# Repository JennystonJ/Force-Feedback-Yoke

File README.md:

# Force Feedback Yoke
A DIY force feedback flight simulator yoke using brushless motors, load cells, and custom firmware to provide simulated control forces.

---

## Overview
- BLDC motors for pitch and roll using torque control.
- Support for load cells. Currently used for force feedback assist (reduces drag felt by user).
- STM32 microcontroller running custom firmware with FOC inspired by SimpleFOC.
- Desktop app for monitoring, setting parameters, handling communication between device and Microsoft Flight Simulator, and calculating forces.

## Features
- Support for 2 axis current/torque control.
- Force feedback assist using load cells to reduce drag.
- USB HID communication.
- Support for constant, spring, and damper effects on both axes.
- Axes travel is software adjustable using the motor as a virtual stopper.

## Technical Details
- Motors: 2 * 57BL95S06-210TF9
- Motor Drivers: 2 * DRV8301 boards
- Microcontroller: STM32H743VGT6
- Sensors:
	- 2 * three phase shunt-based in-line current sensors (INA241)
	- 2 * encoders using AB output (65536 CPR) for lower latency (MT6835)
	- 2 * load cells (20kg) (roll load cell support for mechanical is in progress)
- Software: C firmware, C# desktop app

## Mechanical
- Total pitch travel: ~177 mm, roll travel: ~270 deg
- 3D printed components, aluminum V-slot extrusion for frame. T-slot is also compatible.
- Bearings on all axes, two linear guide rails for linear motion on pitch axis.
- Two-stage belt drive for pitch axis, single belt for roll axis.
- Designed to be modular.

## Desktop App
- Displays live axes positions, and axes force/torque
- Implements custom USB HID communication with device and communication with Microsoft Flight Simulator through SimConnect API.
- Currently supports 2 different force feedback effects, with more being added and existing effects being refined:
	- Supported effects
		- Airspeed stiffness (increases centering force with airspeed)
		- Elevator weight (a constant elevator down force with engine RPM dependent self-centering force).
- Adjustable gains for all force feedback effects in GUI for both pitch and roll axes.
- Travel for both axes are adjustable in GUI.

## Acknowledgements
Algorithms (Clarke & Park transforms) from [SimpleFOC](https://github.com/simplefoc/Arduino-FOC) (MIT License). See LICENSES/LICENSE-SIMPLEFOC.txt for full license.

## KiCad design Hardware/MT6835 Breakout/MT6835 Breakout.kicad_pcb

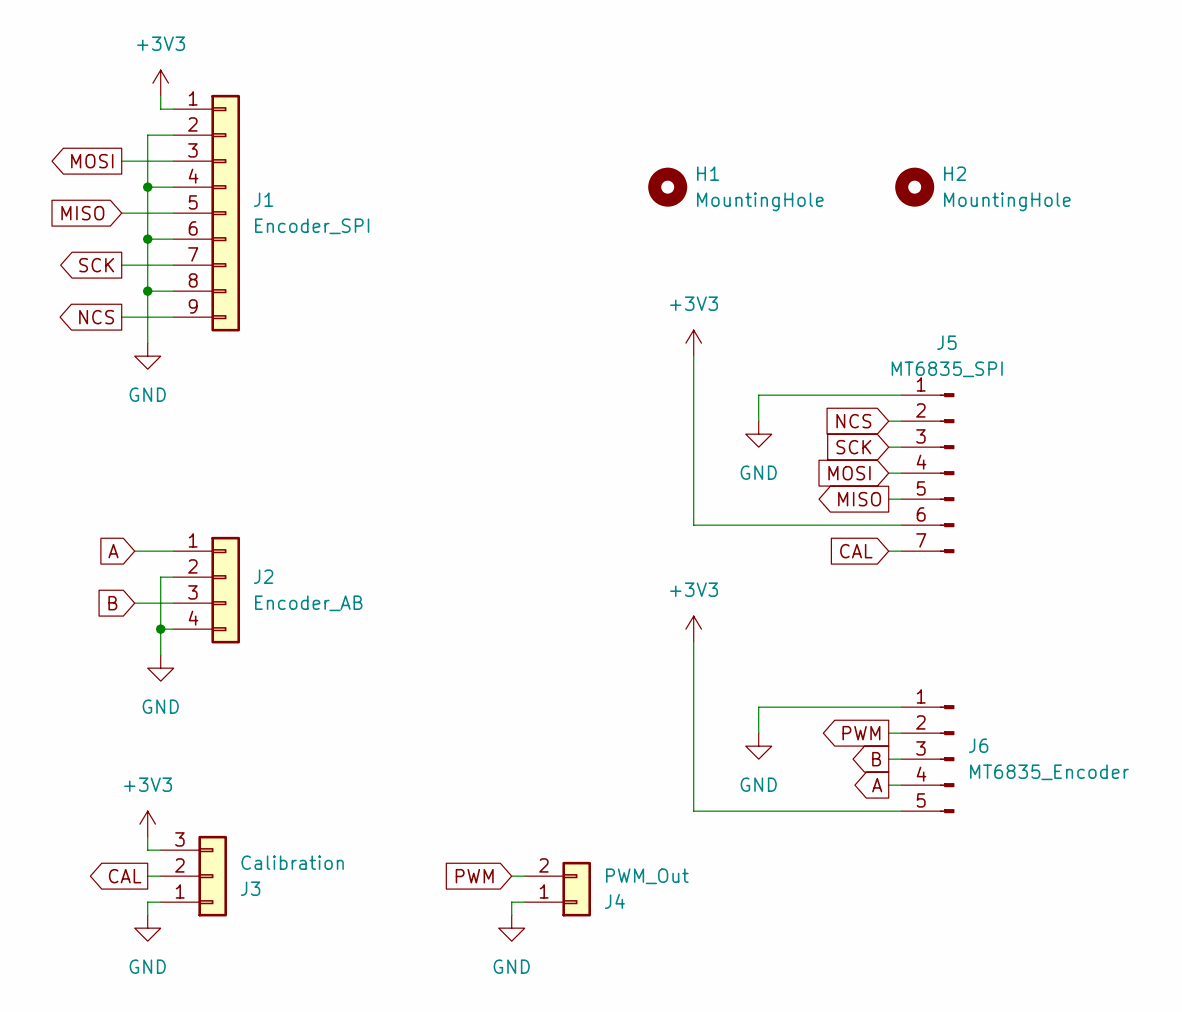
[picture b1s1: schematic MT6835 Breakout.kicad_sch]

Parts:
H1, H2: MountingHole; MountingHole_2.2mm_M2
J1: Encoder_SPI; JST_PH_B9B-PH-K_1x09_P2.00mm_Vertical
J2: Encoder_AB; JST_PH_B4B-PH-K_1x04_P2.00mm_Vertical
J3: Calibration; PinHeader_1x03_P2.54mm_Vertical
J4: PWM_Out; PinHeader_1x02_P2.54mm_Vertical
J5: MT6835_SPI; PinHeader_1x07_P2.54mm_Vertical
J6: MT6835_Encoder; PinHeader_1x05_P2.54mm_Vertical

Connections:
+3V3: J1.1, J3.3, J5.6, J6.5
A: J2.1, J6.4
B: J2.3, J6.3
CAL: J3.2, J5.7
GND: J1.2, J1.4, J1.6, J1.8, J2.2, J2.4, J3.1, J4.1, J5.1, J6.1
MISO: J1.5, J5.5
MOSI: J1.3, J5.4
NCS: J1.9, J5.2
PWM: J4.2, J6.2
SCK: J1.7, J5.3

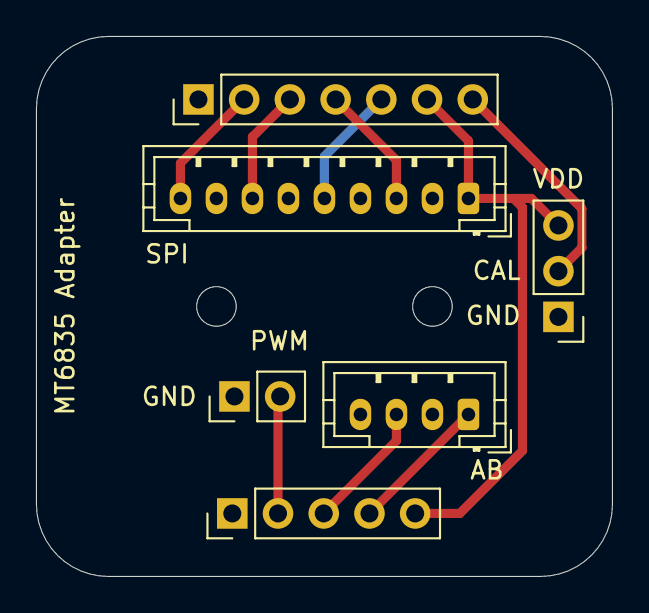
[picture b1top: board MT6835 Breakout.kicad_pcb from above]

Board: 2 copper layers, 32.0 x 30.0 mm, 8 parts (0 on the bottom side), 10 nets.

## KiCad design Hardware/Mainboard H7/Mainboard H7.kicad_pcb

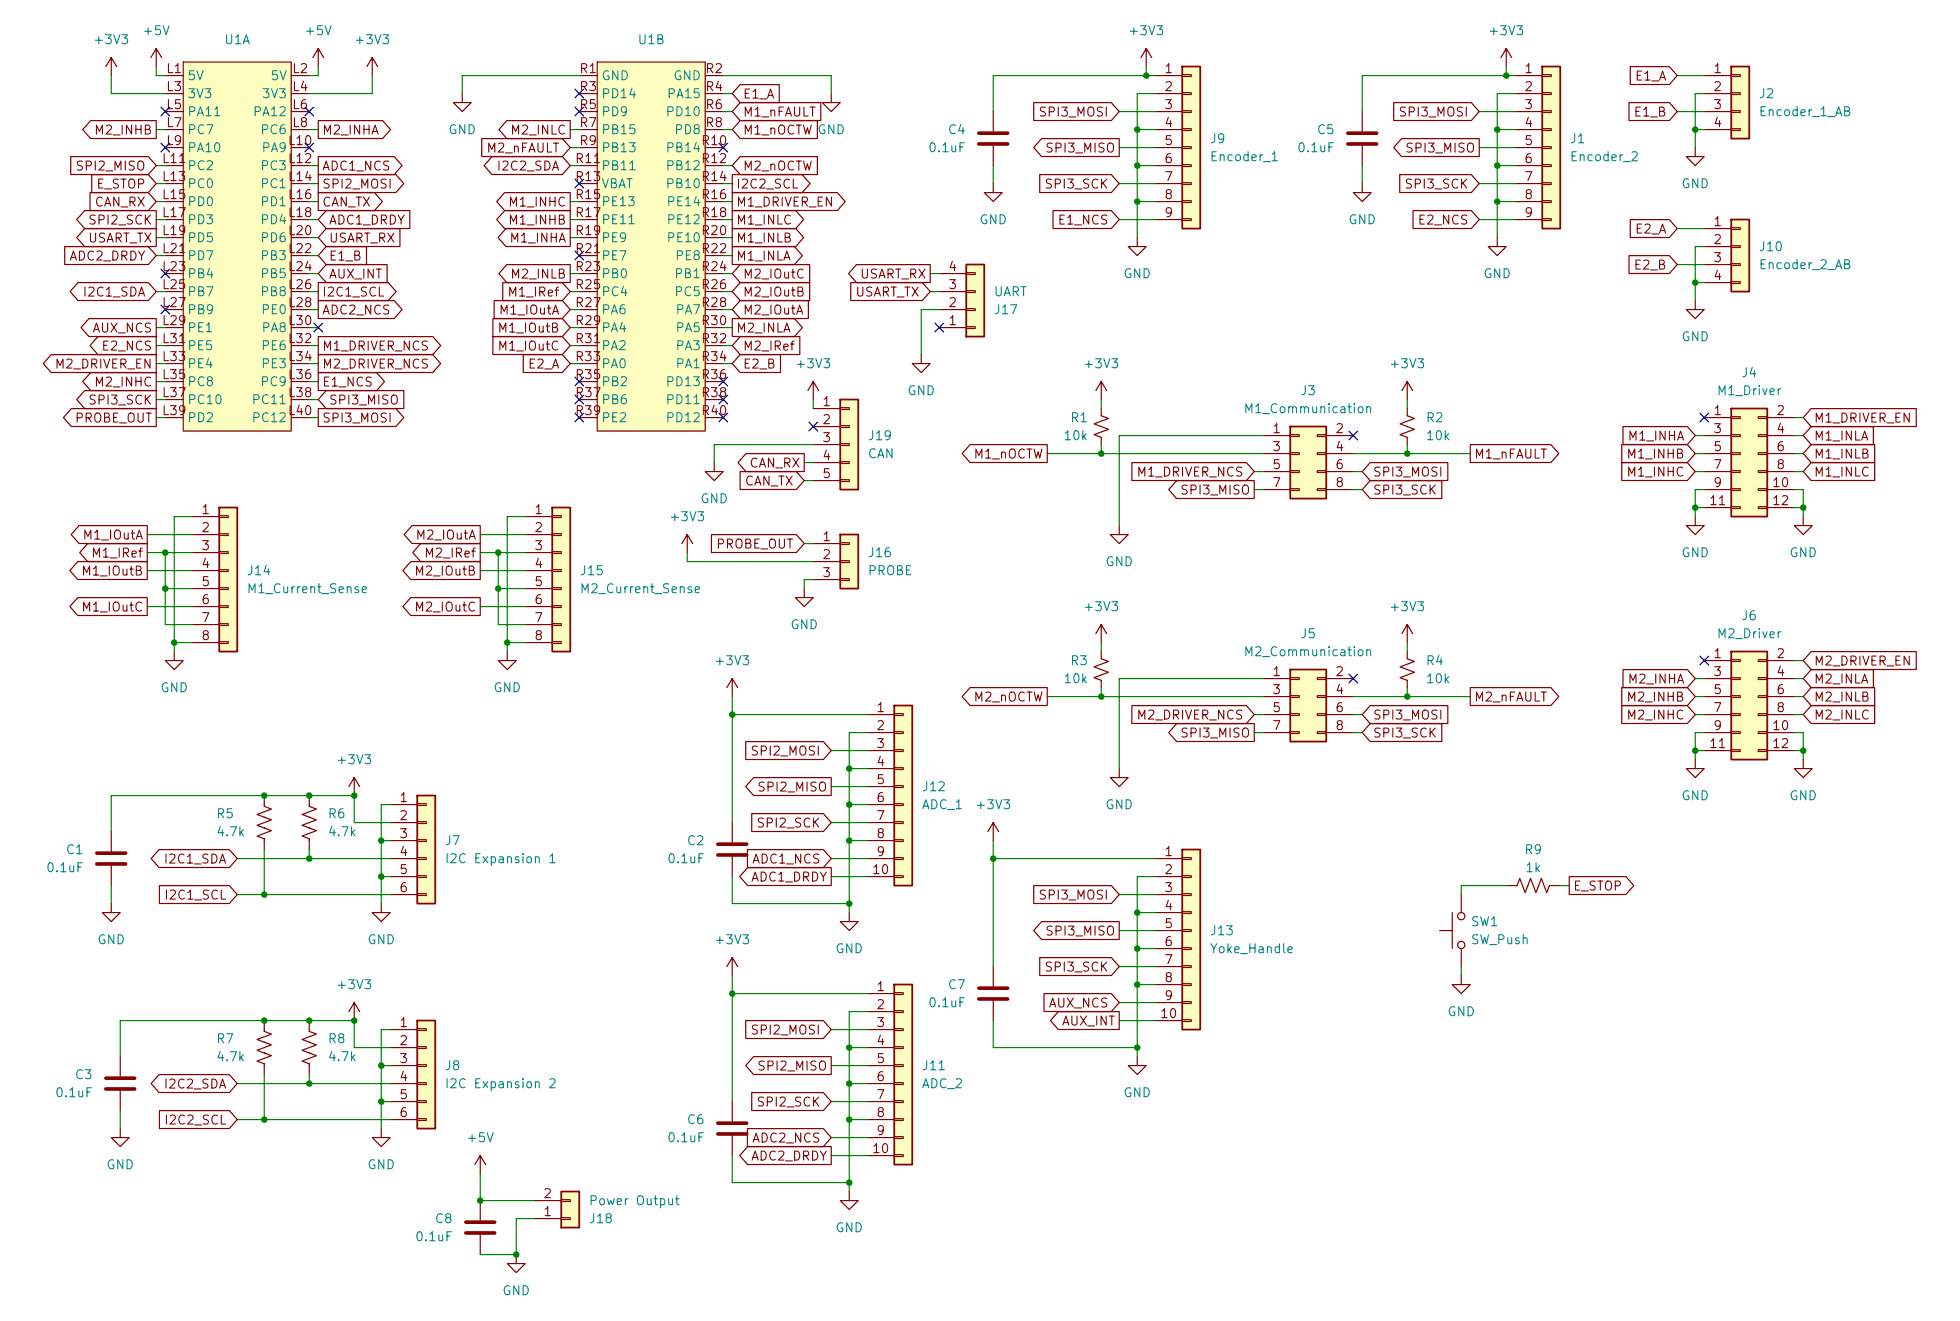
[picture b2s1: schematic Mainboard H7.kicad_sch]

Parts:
C1, C2, C3, C4, C5, C6, C7, C8: 0.1uF; C_0603_1608Metric_Pad1.08x0.95mm_HandSolder
J1: Encoder_2; JST_PH_B9B-PH-K_1x09_P2.00mm_Vertical
J2: Encoder_1_AB; JST_PH_B4B-PH-K_1x04_P2.00mm_Vertical
J3: M1_Communication; PinHeader_2x04_P2.54mm_Vertical
J4: M1_Driver; PinHeader_2x06_P2.54mm_Vertical
J5: M2_Communication; PinHeader_2x04_P2.54mm_Vertical
J6: M2_Driver; PinHeader_2x06_P2.54mm_Vertical
J7: I2C Expansion 1; JST_PH_B6B-PH-K_1x06_P2.00mm_Vertical
J8: I2C Expansion 2; JST_PH_B6B-PH-K_1x06_P2.00mm_Vertical
J9: Encoder_1; JST_PH_B9B-PH-K_1x09_P2.00mm_Vertical
J10: Encoder_2_AB; JST_PH_B4B-PH-K_1x04_P2.00mm_Vertical
J11: ADC_2; JST_PH_B10B-PH-K_1x10_P2.00mm_Vertical
J12: ADC_1; JST_PH_B10B-PH-K_1x10_P2.00mm_Vertical
J13: Yoke_Handle; JST_PH_B10B-PH-K_1x10_P2.00mm_Vertical
J14: M1_Current_Sense; JST_PH_B8B-PH-K_1x08_P2.00mm_Vertical
J15: M2_Current_Sense; JST_PH_B8B-PH-K_1x08_P2.00mm_Vertical
J16: PROBE; PinHeader_1x03_P2.54mm_Vertical
J17: UART; PinHeader_1x04_P2.54mm_Vertical
J18: Power Output; PinHeader_1x02_P2.54mm_Vertical
J19: CAN; PinHeader_1x05_P2.54mm_Vertical
R1, R2, R3, R4: 10k; R_0603_1608Metric_Pad0.98x0.95mm_HandSolder
R5, R6, R7, R8: 4.7k; R_0603_1608Metric_Pad0.98x0.95mm_HandSolder
R9: 1k; R_0603_1608Metric_Pad0.98x0.95mm_HandSolder
SW1: SW_Push; JST_PH_B2B-PH-K_1x02_P2.00mm_Vertical
U1: FK743M3-VGT6

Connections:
+3V3: C1.1, C2.1, C3.1, C4.1, C5.1, C6.1, C7.1, J1.1, J7.2, J8.2, J9.1, J11.1, J12.1, J13.1, J16.2, J19.1, R1.1, R2.1, R3.1, R4.1, R5.1, R6.1, R7.1, R8.1, U1.L3 (3V3), U1.L4 (3V3)
+5V: C8.1, J18.2, U1.L1 (5V), U1.L2 (5V)
ADC1_DRDY: J12.10, U1.L18 (PD4)
ADC1_NCS: J12.9, U1.L12 (PC3)
ADC2_DRDY: J11.10, U1.L21 (PD7)
ADC2_NCS: J11.9, U1.L28 (PE0)
AUX_INT: J13.10, U1.L24 (PB5)
AUX_NCS: J13.9, U1.L29 (PE1)
CAN_RX: J19.4, U1.L15 (PD0)
CAN_TX: J19.5, U1.L16 (PD1)
E1_A: J2.1, U1.R4 (PA15)
E1_B: J2.3, U1.L22 (PB3)
E1_NCS: J9.9, U1.L36 (PC9)
E2_A: J10.1, U1.R33 (PA0)
E2_B: J10.3, U1.R34 (PA1)
E2_NCS: J1.9, U1.L31 (PE5)
E_STOP: R9.1, U1.L13 (PC0)
GND: C1.2, C2.2, C3.2, C4.2, C5.2, C6.2, C7.2, C8.2, J1.2, J1.4, J1.6, J1.8, J2.2, J2.4, J3.1, J4.9, J4.10, J4.11, J4.12, J5.1, J6.9, J6.10, J6.11, J6.12, J7.1, J7.3, J7.5, J8.1, J8.3, J8.5, J9.2, J9.4, J9.6, J9.8, J10.2, J10.4, J11.2, J11.4, J11.6, J11.8, J12.2, J12.4, J12.6, J12.8, J13.2, J13.4, J13.6, J13.8, J14.1, J14.8, J15.1, J15.8, J16.3, J17.2, J18.1, J19.3, SW1.1, U1.R1 (GND), U1.R2 (GND)
I2C1_SCL: J7.6, R5.2, U1.L26 (PB8)
I2C1_SDA: J7.4, R6.2, U1.L25 (PB7)
I2C2_SCL: J8.6, R7.2, U1.R14 (PB10)
I2C2_SDA: J8.4, R8.2, U1.R11 (PB11)
M1_DRIVER_EN: J4.2, U1.R16 (PE14)
M1_DRIVER_NCS: J3.5, U1.L32 (PE6)
M1_INHA: J4.3, U1.R19 (PE9)
M1_INHB: J4.5, U1.R17 (PE11)
M1_INHC: J4.7, U1.R15 (PE13)
M1_INLA: J4.4, U1.R22 (PE8)
M1_INLB: J4.6, U1.R20 (PE10)
M1_INLC: J4.8, U1.R18 (PE12)
M1_IOutA: J14.2, U1.R27 (PA6)
M1_IOutB: J14.4, U1.R29 (PA4)
M1_IOutC: J14.6, U1.R31 (PA2)
M1_IRef: J14.3, J14.5, J14.7, U1.R25 (PC4)
M1_nFAULT: J3.4, R2.2, U1.R6 (PD10)
M1_nOCTW: J3.3, R1.2, U1.R8 (PD8)
M2_DRIVER_EN: J6.2, U1.L33 (PE4)
M2_DRIVER_NCS: J5.5, U1.L34 (PE3)
M2_INHA: J6.3, U1.L8 (PC6)
M2_INHB: J6.5, U1.L7 (PC7)
M2_INHC: J6.7, U1.L35 (PC8)
M2_INLA: J6.4, U1.R30 (PA5)
M2_INLB: J6.6, U1.R23 (PB0)
M2_INLC: J6.8, U1.R7 (PB15)
M2_IOutA: J15.2, U1.R28 (PA7)
M2_IOutB: J15.4, U1.R26 (PC5)
M2_IOutC: J15.6, U1.R24 (PB1)
M2_IRef: J15.3, J15.5, J15.7, U1.R32 (PA3)
M2_nFAULT: J5.4, R4.2, U1.R9 (PB13)
M2_nOCTW: J5.3, R3.2, U1.R12 (PB12)
unnamed: R9.2, SW1.2
PROBE_OUT: J16.1, U1.L39 (PD2)
SPI2_MISO: J11.5, J12.5, U1.L11 (PC2)
SPI2_MOSI: J11.3, J12.3, U1.L14 (PC1)
SPI2_SCK: J11.7, J12.7, U1.L17 (PD3)
SPI3_MISO: J1.5, J3.7, J5.7, J9.5, J13.5, U1.L38 (PC11)
SPI3_MOSI: J1.3, J3.6, J5.6, J9.3, J13.3, U1.L40 (PC12)
SPI3_SCK: J1.7, J3.8, J5.8, J9.7, J13.7, U1.L37 (PC10)
USART_RX: J17.4, U1.L20 (PD6)
USART_TX: J17.3, U1.L19 (PD5)

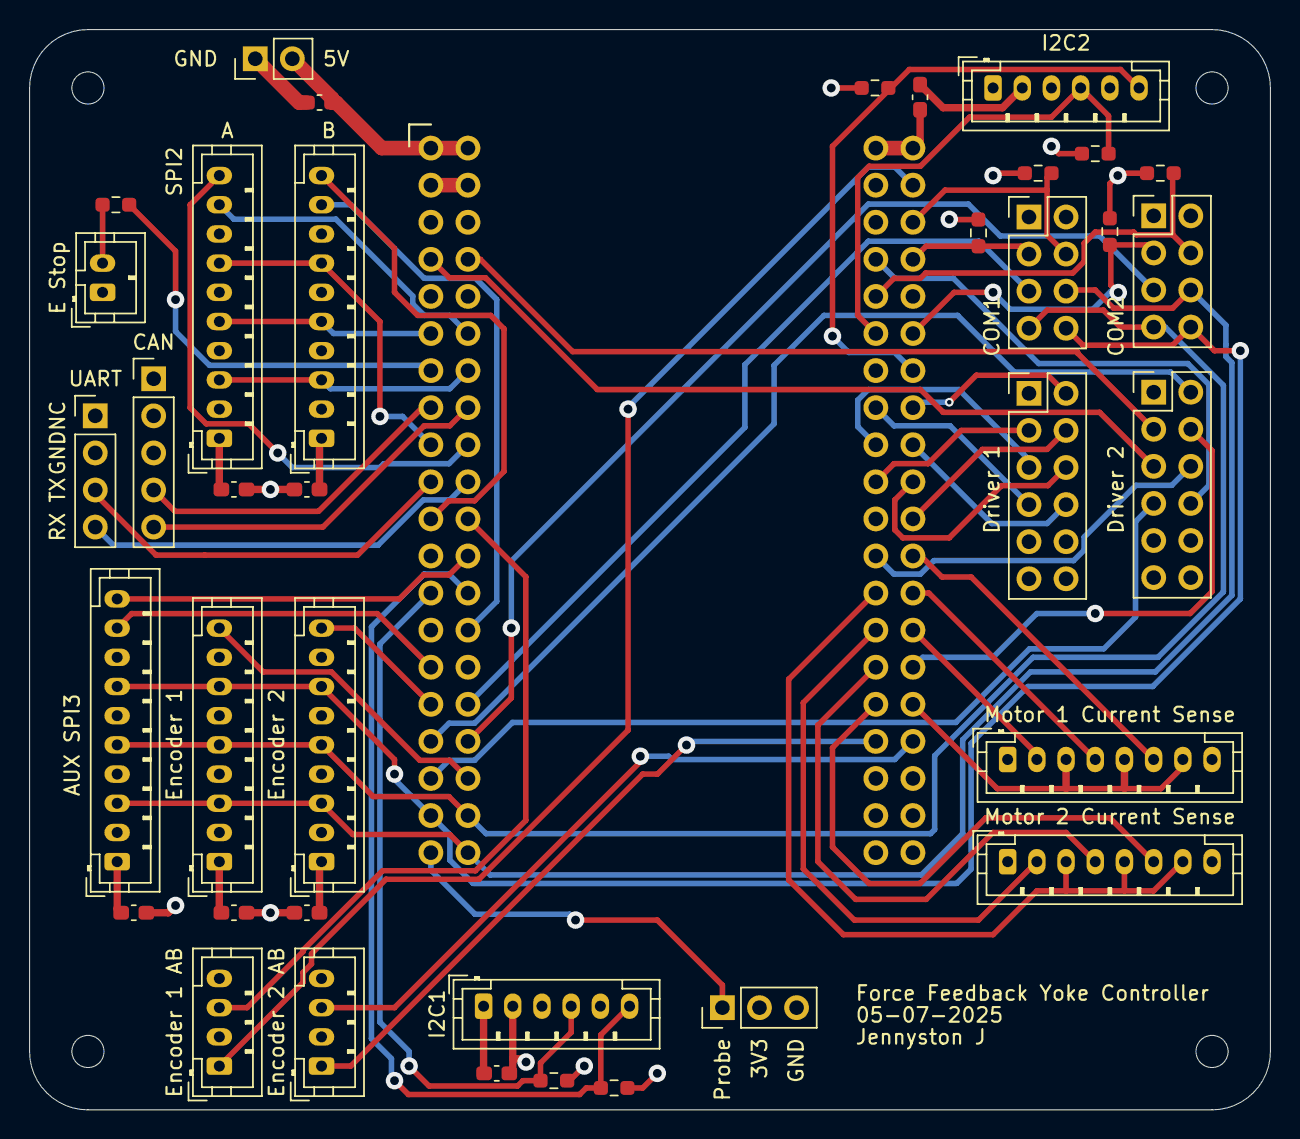
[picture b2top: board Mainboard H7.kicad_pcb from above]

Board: 4 copper layers, 85.0 x 74.0 mm, 38 parts (0 on the bottom side), 60 nets.

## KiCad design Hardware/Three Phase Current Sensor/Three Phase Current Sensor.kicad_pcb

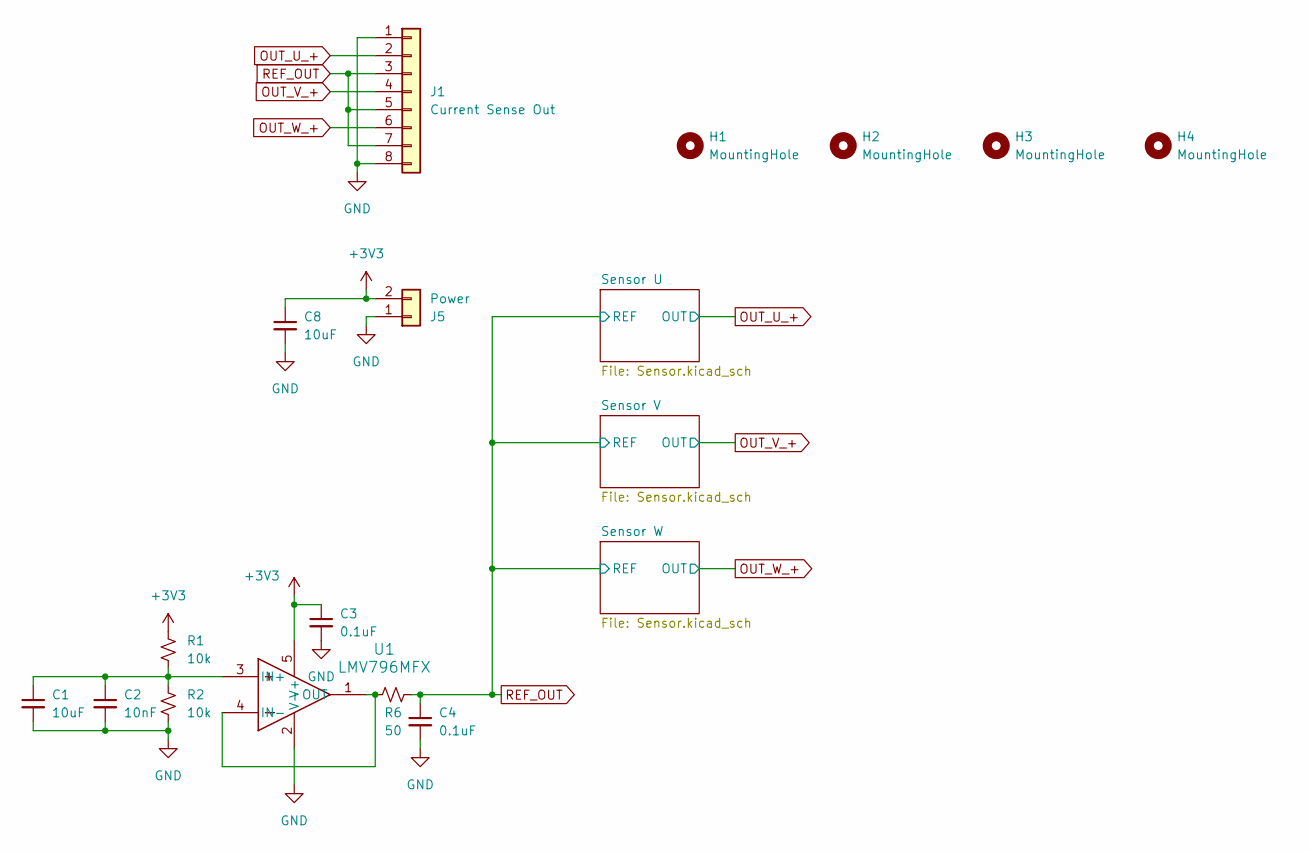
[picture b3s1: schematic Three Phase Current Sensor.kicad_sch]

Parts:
C1, C8: 10uF; C_0603_1608Metric
C2: 10nF; C_0603_1608Metric
C3, C4: 0.1uF; C_0603_1608Metric
H1, H2, H3, H4: MountingHole; MountingHole_2.2mm_M2
J1: Current Sense Out; JST_PH_B8B-PH-K_1x08_P2.00mm_Vertical
J5: Power; Molex_KK-254_AE-6410-02A_1x02_P2.54mm_Vertical
R1, R2: 10k; R_0603_1608Metric
R6: 50; R_0603_1608Metric
U1: LMV796MFX; DBV0005A-MFG

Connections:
+3V3: C3.1, C8.1, J5.2, R1.2, U1.5 (V+); also elsewhere on the board
GND: C1.2, C2.2, C3.2, C4.2, C8.2, J1.1, J1.8, J5.1, R2.1, U1.2 (V-); also elsewhere on the board
unnamed: C1.1, C2.1, R1.1, R2.2, U1.3 (IN+)
unnamed: R6.2, U1.1 (OUT), U1.4 (IN-)
OUT_U_+: J1.2; also elsewhere on the board
OUT_V_+: J1.4; also elsewhere on the board
OUT_W_+: J1.6; also elsewhere on the board
REF_OUT: C4.1, J1.3, J1.5, J1.7, R6.1; also elsewhere on the board

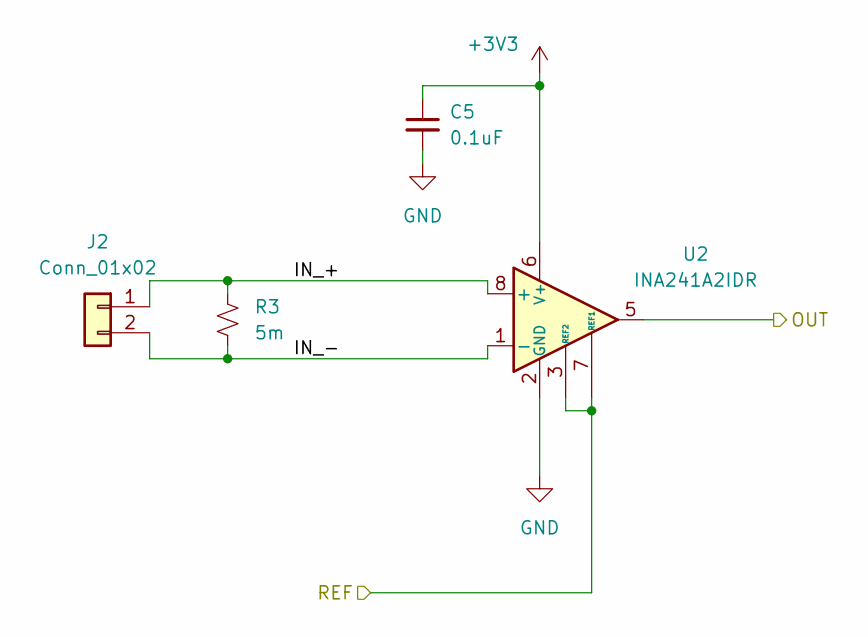
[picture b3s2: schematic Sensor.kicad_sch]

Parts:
C5: 0.1uF; C_0603_1608Metric
J2: Conn_01x02; TerminalBlock_Phoenix_MKDS-1,5-2-5.08_1x02_P5.08mm_Horizont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
R3: 5m; R_2512_6332Metric
U2: INA241A2IDR; SOIC-8_3.9x4.9mm_P1.27mm

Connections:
+3V3: C5.1, U2.6 (V+); also elsewhere on the board
/Sensor U/IN_+: J2.1, R3.1, U2.8 (+)
/Sensor U/IN_-: J2.2, R3.2, U2.1 (-)
GND: C5.2, U2.2 (GND), U2.4 (GND); also elsewhere on the board
OUT_U_+: U2.5; also elsewhere on the board
REF_OUT: U2.3 (REF2), U2.7 (REF1); also elsewhere on the board

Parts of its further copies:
C6, C7: 0.1uF; C_0603_1608Metric
J3, J4: Conn_01x02; TerminalBlock_Phoenix_MKDS-1,5-2-5.08_1x02_P5.08mm_Horizont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
R4, R5: 5m; R_2512_6332Metric
U3, U4: INA241A2IDR; SOIC-8_3.9x4.9mm_P1.27mm

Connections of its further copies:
+3V3: C6.1, C7.1, U3.6 (V+), U4.6 (V+); also elsewhere on the board
/Sensor V/IN_+: J3.1, R4.1, U3.8 (+)
/Sensor V/IN_-: J3.2, R4.2, U3.1 (-)
/Sensor W/IN_+: J4.1, R5.1, U4.8 (+)
/Sensor W/IN_-: J4.2, R5.2, U4.1 (-)
GND: C6.2, C7.2, U3.2 (GND), U3.4 (GND), U4.2 (GND), U4.4 (GND); also elsewhere on the board
OUT_V_+: U3.5; also elsewhere on the board
OUT_W_+: U4.5; also elsewhere on the board
REF_OUT: U3.3 (REF2), U3.7 (REF1), U4.3 (REF2), U4.7 (REF1); also elsewhere on the board

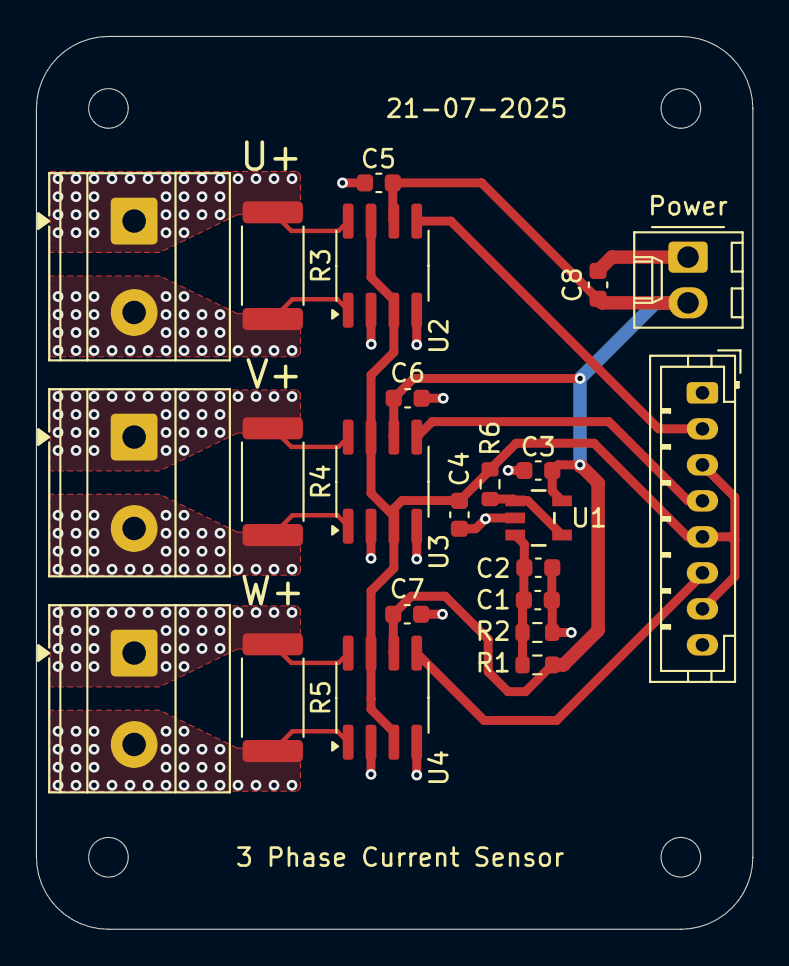
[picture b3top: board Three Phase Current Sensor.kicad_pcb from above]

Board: 2 copper layers, 39.8 x 49.6 mm, 27 parts (0 on the bottom side), 14 nets.

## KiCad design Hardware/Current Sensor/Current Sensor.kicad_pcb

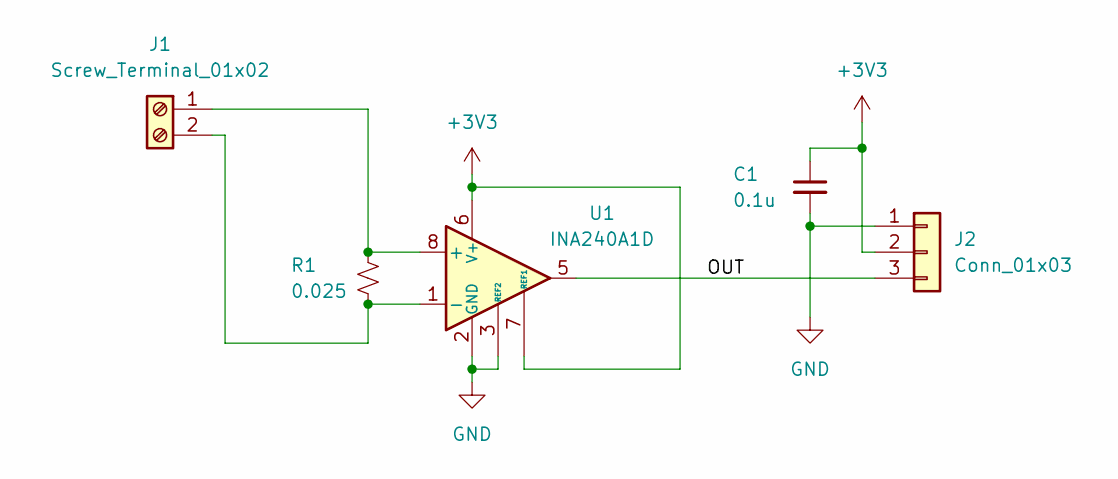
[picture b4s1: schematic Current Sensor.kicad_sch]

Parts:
C1: 0.1u; R_0603_1608Metric
J1: Screw_Terminal_01x02; TerminalBlock_Phoenix_PT-1,5-2-3.5-H_1x02_P3.50mm_Horizontal
J2: Conn_01x03; PinHeader_1x03_P2.54mm_Vertical
R1: 0.025; R_2512_6332Metric
U1: INA240A1D; SOIC-8_3.9x4.9mm_P1.27mm

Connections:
+3V3: C1.1, J2.2, U1.6 (V+), U1.7 (REF1)
/OUT: J2.3, U1.5
GND: C1.2, J2.1, U1.2 (GND), U1.3 (REF2), U1.4 (GND)
unnamed: J1.1, R1.1, U1.8 (+)
unnamed: J1.2, R1.2, U1.1 (-)

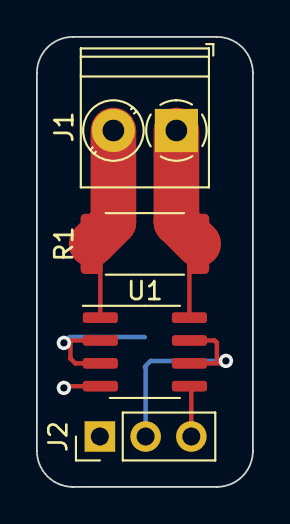
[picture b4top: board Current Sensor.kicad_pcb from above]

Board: 2 copper layers, 12.0 x 25.0 mm, 5 parts (1 on the bottom side), 5 nets.

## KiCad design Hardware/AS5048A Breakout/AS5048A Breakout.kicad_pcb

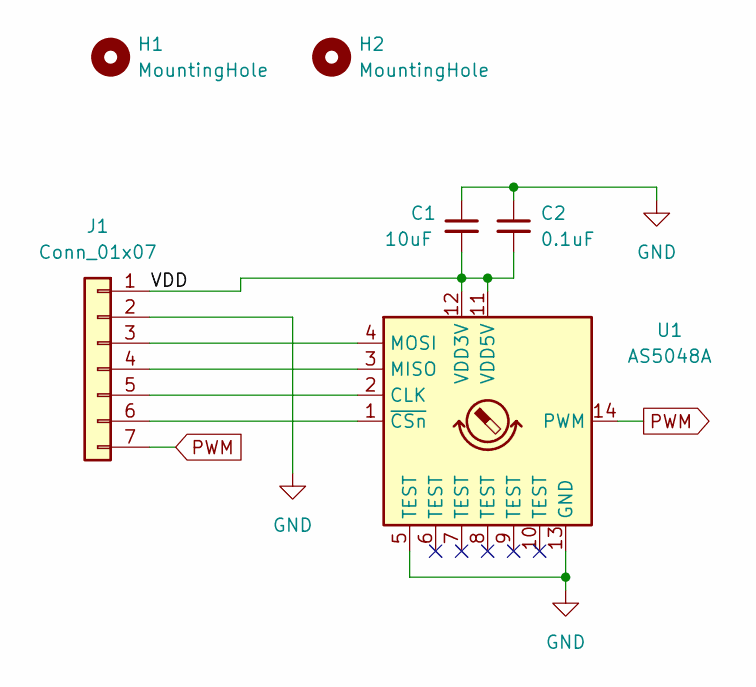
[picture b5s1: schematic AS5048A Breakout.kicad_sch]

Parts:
C1: 10uF; C_0603_1608Metric
C2: 0.1uF; C_0603_1608Metric
H1, H2: MountingHole
J1: Conn_01x07
U1: AS5048A; TSSOP-14_4.4x5mm_P0.65mm

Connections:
/VDD: C1.2, C2.2, J1.1, U1.11 (VDD5V), U1.12 (VDD3V)
GND: C1.1, C2.1, J1.2, U1.5 (TEST), U1.13 (GND)
unnamed: J1.3, U1.4 (MOSI)
unnamed: J1.4, U1.3 (MISO)
unnamed: J1.5, U1.2 (CLK)
unnamed: J1.6, U1.1 (~CSn)
PWM: J1.7, U1.14 (PWM)

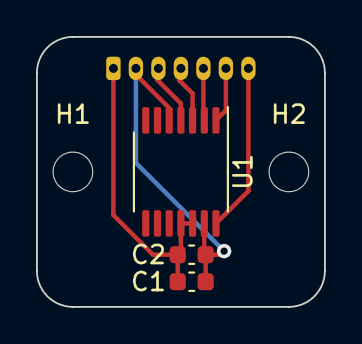
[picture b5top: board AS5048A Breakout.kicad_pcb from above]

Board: 2 copper layers, 16.0 x 15.0 mm, 6 parts (1 on the bottom side), 7 nets.

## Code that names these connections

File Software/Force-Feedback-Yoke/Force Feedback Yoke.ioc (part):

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Mcu.Name=STM32H743VGTx
Mcu.Package=LQFP100
Mcu.UserName=STM32H743VGTx
PA0.Signal=S_TIM5_CH1
PA1.Signal=S_TIM5_CH2
PA10.Mode=Asynchronous
PA10.Signal=USART1_RX
PA11.Mode=Device_Only
PA11.Signal=USB_OTG_FS_DM
PA12.Mode=Device_Only
PA12.Signal=USB_OTG_FS_DP
PA13\ (JTMS/SWDIO).Mode=Serial_Wire
PA13\ (JTMS/SWDIO).Signal=DEBUG_JTMS-SWDIO
PA14\ (JTCK/SWCLK).Mode=Serial_Wire
PA14\ (JTCK/SWCLK).Signal=DEBUG_JTCK-SWCLK
PA15\ (JTDI).GPIOParameters=GPIO_Label
PA15\ (JTDI).GPIO_Label=ENC_PITCH_A
PA15\ (JTDI).Signal=S_TIM2_CH1_ETR
PA2.Signal=ADCx_INP14
PA3.Signal=ADCx_INP15
PA4.Signal=ADCx_INP18
PA5.Mode=PWM Generation1 CH1 CH1N
PA5.Signal=TIM8_CH1N
PA6.Signal=ADCx_INP3
PA7.Signal=ADCx_INP7
PA9.Mode=Asynchronous
PA9.Signal=USART1_TX
PB0.Mode=PWM Generation2 CH2 CH2N
PB0.Signal=TIM8_CH2N
PB1.Signal=ADCx_INP5
PB10.Mode=I2C
PB10.Signal=I2C2_SCL
PB11.Mode=I2C
PB11.Signal=I2C2_SDA
PB12.GPIOParameters=GPIO_Label
PB12.GPIO_Label=M2_NOCTW
PB12.Signal=GPXTI12
PB13.GPIOParameters=GPIO_Label
PB13.GPIO_Label=M2_NFAULT
PB13.Signal=GPXTI13
PB14.Signal=S_TIM12_CH1
PB15.Mode=PWM Generation3 CH3 CH3N
PB15.Signal=TIM8_CH3N
PB2.Mode=Single Bank 1
PB2.Signal=QUADSPI_CLK
PB3\ (JTDO/TRACESWO).GPIOParameters=GPIO_Label
PB3\ (JTDO/TRACESWO).GPIO_Label=ENC_PITCH_B
PB3\ (JTDO/TRACESWO).Signal=S_TIM2_CH2
PB4\ (NJTRST).Signal=S_TIM3_CH1
PB5.GPIOParameters=GPIO_Label
PB5.GPIO_Label=AUX_INT
PB5.Signal=GPXTI5
PB6.GPIOParameters=PinAttribute
PB6.Mode=Single Bank 1
PB6.PinAttribute=Free
PB6.Signal=QUADSPI_BK1_NCS
PB7.GPIOParameters=PinAttribute
PB7.Mode=I2C
PB7.PinAttribute=Free
PB7.Signal=I2C1_SDA
PB8.GPIOParameters=PinAttribute
PB8.Mode=I2C
PB8.PinAttribute=Free
PB8.Signal=I2C1_SCL
PC0.GPIOParameters=GPIO_PuPd,GPIO_Label,GPIO_ModeDefaultEXTI
PC0.GPIO_Label=E_STOP
PC0.GPIO_ModeDefaultEXTI=GPIO_MODE_IT_RISING_FALLING
PC0.GPIO_PuPd=GPIO_PULLUP
PC0.Signal=GPXTI0
PC1.Mode=Full_Duplex_Master
PC1.Signal=SPI2_MOSI
PC10.Mode=Full_Duplex_Master
PC10.Signal=SPI3_SCK
PC11.GPIOParameters=GPIO_Speed
PC11.GPIO_Speed=GPIO_SPEED_FREQ_LOW
PC11.Mode=Full_Duplex_Master
PC11.Signal=SPI3_MISO
PC12.GPIOParameters=GPIO_Speed
PC12.GPIO_Speed=GPIO_SPEED_FREQ_LOW
PC12.Mode=Full_Duplex_Master
PC12.Signal=SPI3_MOSI
PC13.GPIOParameters=GPIO_Label
PC13.GPIO_Label=STATUS_LED
PC13.Signal=GPIO_Output
PC14-OSC32_IN\ (OSC32_IN).Mode=LSE-External-Oscillator
PC14-OSC32_IN\ (OSC32_IN).Signal=RCC_OSC32_IN
PC15-OSC32_OUT\ (OSC32_OUT).Mode=LSE-External-Oscillator
PC15-OSC32_OUT\ (OSC32_OUT).Signal=RCC_OSC32_OUT
PC2_C.Mode=Full_Duplex_Master
PC2_C.Signal=SPI2_MISO
PC3_C.GPIOParameters=PinState,GPIO_Label
PC3_C.GPIO_Label=ADC1_NCS
PC3_C.PinState=GPIO_PIN_SET
PC3_C.Signal=GPIO_Output
PC4.Signal=ADCx_INP4
PC5.Signal=ADCx_INP8
PC6.Signal=S_TIM8_CH1
PC7.Signal=S_TIM8_CH2
PC8.Signal=S_TIM8_CH3
PC9.GPIOParameters=PinState,GPIO_Label
PC9.GPIO_Label=E1_NCS
PC9.PinState=GPIO_PIN_SET
PC9.Signal=GPIO_Output
PD0.Mode=FDCAN_Activate
PD0.Signal=FDCAN1_RX
PD1.Mode=FDCAN_Activate
PD1.Signal=FDCAN1_TX
PD10.GPIOParameters=GPIO_Label
PD10.GPIO_Label=M1_NFAULT
PD10.Signal=GPXTI10
PD11.Mode=Single Bank 1
PD11.Signal=QUADSPI_BK1_IO0
PD12.Mode=Single Bank 1
PD12.Signal=QUADSPI_BK1_IO1
PD13.Mode=Single Bank 1
PD13.Signal=QUADSPI_BK1_IO3
PD2.GPIOParameters=GPIO_Speed,GPIO_Label
PD2.GPIO_Label=PROBE_OUT
PD2.GPIO_Speed=GPIO_SPEED_FREQ_MEDIUM
PD2.Signal=GPIO_Output
PD3.Mode=Full_Duplex_Master
PD3.Signal=SPI2_SCK
PD4.GPIOParameters=GPIO_Label,GPIO_ModeDefaultEXTI
PD4.GPIO_Label=ADC1_DRDY
PD4.GPIO_ModeDefaultEXTI=GPIO_MODE_IT_RISING
PD4.Signal=GPXTI4
PD5.Mode=Asynchronous
PD5.Signal=USART2_TX
PD6.Mode=Asynchronous
PD6.Signal=USART2_RX
PD7.GPIOParameters=GPIO_Label
PD7.GPIO_Label=ADC2_DRDY
PD7.Signal=GPXTI7
PD8.GPIOParameters=GPIO_Label
PD8.GPIO_Label=M1_NOCTW
PD8.Signal=GPXTI8
PE0.GPIOParameters=PinState,GPIO_Label,PinAttribute
PE0.GPIO_Label=ADC2_NCS
PE0.PinAttribute=Free
PE0.PinState=GPIO_PIN_SET
PE0.Signal=GPIO_Output
PE1.GPIOParameters=PinState,GPIO_Label,PinAttribute
PE1.GPIO_Label=AUX_NCS
PE1.PinAttribute=Free
PE1.PinState=GPIO_PIN_SET
PE1.Signal=GPIO_Output
PE10.Mode=PWM Generation2 CH2 CH2N
PE10.Signal=TIM1_CH2N
PE11.Signal=S_TIM1_CH2
PE12.Mode=PWM Generation3 CH3 CH3N
PE12.Signal=TIM1_CH3N
PE13.Signal=S_TIM1_CH3
PE14.GPIOParameters=GPIO_Label
PE14.GPIO_Label=M1_DRIVER_EN
PE14.Signal=GPIO_Output
PE2.GPIOParameters=PinAttribute
PE2.Mode=Single Bank 1
PE2.PinAttribute=Free
PE2.Signal=QUADSPI_BK1_IO2
PE3.GPIOParameters=PinState,GPIO_Label,PinAttribute
PE3.GPIO_Label=M2_DRIVER_NCS
PE3.PinAttribute=Free
PE3.PinState=GPIO_PIN_SET
PE3.Signal=GPIO_Output
PE4.GPIOParameters=GPIO_Label,PinAttribute
PE4.GPIO_Label=M2_DRIVER_EN
PE4.PinAttribute=Free
PE4.Signal=GPIO_Output
PE5.GPIOParameters=PinState,GPIO_Label,PinAttribute
PE5.GPIO_Label=E2_NCS
PE5.PinAttribute=Free
PE5.PinState=GPIO_PIN_SET
PE5.Signal=GPIO_Output
PE6.GPIOParameters=PinState,GPIO_Label,PinAttribute
PE6.GPIO_Label=M1_DRIVER_NCS
PE6.PinAttribute=Free
PE6.PinState=GPIO_PIN_SET
PE6.Signal=GPIO_Output
PE8.Mode=PWM Generation1 CH1 CH1N
PE8.Signal=TIM1_CH1N
PE9.Signal=S_TIM1_CH1
PH0-OSC_IN\ (PH0).Mode=HSE-External-Oscillator
PH0-OSC_IN\ (PH0).Signal=RCC_OSC_IN
PH1-OSC_OUT\ (PH1).Mode=HSE-External-Oscillator
PH1-OSC_OUT\ (PH1).Signal=RCC_OSC_OUT
RCC.SYSCLKFreq_VALUE=480000000
RCC.SYSCLKSource=RCC_SYSCLKSOURCE_PLLCLK
board=custom

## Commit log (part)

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2023-04-29 Initial commit.
2023-05-24 Unit testing added. Force feedback spring force tested.
2023-05-25 Current sensing added (not yet implemented). Damper and spring force added.
2023-06-20 Major changes made. Code currently configured to run alongside MSFSForceFeedbackController.
2023-06-20 AS5048A breakout board added.
2023-06-20 Project renamed from Force-Feedback-Yoke-Test to Force-Feedback-Yoke.
2023-06-23 Current sensor schematic complete.
2023-09-29 USB device backup updated.
2023-09-29 Added gitignore.
2023-09-29 Added report ID to USB report descriptor.
2023-09-29 gitignore is now working.
2023-09-29 Fixed bug with FFBComputeSpringForce parameters switched. Reverted USB report descriptor.
2023-10-02 Speed calculation now works for both directions.
2023-10-02 Endstop feature added.
2023-10-06 Added report ID (0x01) to report descriptor.
2023-10-06 Added report descriptor for both receiving FFB data and transmitting aileron position.
2023-10-07 Increased out report buffer size to 5 bytes.
2023-10-07 Added function for initializing FFBPeriodic structure and calculating FFB periodic force.
2023-10-07 Added unit tests for FFB periodic functions.
2023-10-07 Added test code for FFB periodic functions.
2023-10-13 Increased report size to accommodate periodic forces.
2023-10-13 Added time divider for counting time in ms in timer 6 ISR.
2023-10-13 Updated USB backup.
2023-10-13 Removed time divider logic from timer 6 ISR. Replaced time measurement code with HAL_GetTick()
2023-10-20 In process of moving the parsing of usb reports to usb_report.
2023-11-24 Added UsbReport to main.
2023-11-24 Modified syntax for multi-line strings.
2023-11-24 Added unit tests for usb_report.c.
2024-07-12 Added packet parser and USB report.
2024-07-12 Modified pinout, regenerated code.
2024-07-12 Restructured project.
2024-07-12 Simplified code by using ConstrainFloat function.
2024-07-12 Moved utilites to utilities directory.
2024-07-12 Added encoder with unit tests.
2024-07-12 Removed Abs static function, used utilites instead.
2024-07-13 Refactored code.
2024-07-13 Added AS5600 encoder.
2024-07-13 Removed .cyclo files.
2024-07-16 Refactored code to decouple hardware from software.
2024-07-16 Modified pin labels, added accept button.
2024-07-16 Added code for handling buttons.
2024-07-16 Migrated code from main to app and bsp (Board Support Package).
2024-07-19 Created FFBPeriodicUpdateTime function to keep track of time for periodic forces.
2024-07-19 Replaced time variable in FFBPeriodicParam struct to timeInMs (defined in source file).
2024-07-20 Added FFBSpringParam struct.
2024-07-20 Reverted changes: Removed FFBPeriodicUpdateTime function.
2024-07-25 Removed gain from force calculation. force_feedback_controller is now responsible for gain.
2024-07-25 Added FFB parameters to FFBController structure. Added corresponding set functions. Added FFBCalcForces function.
2024-07-25 Added initialization code. Added ApplicationUpdate function.
2024-07-25 Added call to ApplicationUpdate function from timer interrrupt callback.
2024-07-26 Added wrapper for HAL_Delay function.
2024-08-01 Migrated device firmware to STM32F411CE.
2024-08-10 Changed FFB controller states. Removed FFB_HOMING, added FFB_IDLE.
2024-08-10 Added direction power scale.
2024-08-10 Changed motor power max due to change in PWM resolution.
2024-08-10 Added application update functions to timer ISR.
2024-08-10 Fixed PWM not starting.
2024-08-10 Removed ignored files.
2024-10-23 Added Google Test framework.
2024-10-26 Added support for C++ compilation for unit tests.
2024-10-26 Modified device configuration.
2024-10-26 Modified for better decoupling.
2024-10-26 Test code for force feedback assist (unimplemented).
2024-10-26 Added control range and assist.
2024-10-26 Added byte parsing.
2024-10-26 Changed to obtain sensor count through interface instead.
2024-10-26 Modified code as per STMicroelectronics' custom USB HID tutorial and modified custom HID endpoint sizes.
2024-10-26 Added motor driver enable pins.
2024-10-26 Updated makefiles.
2024-10-26 Removed old backup since it's no longer needed.
2024-10-26 Updated build file.
2024-10-26 Backup of USB device library files (STM32CubeIDE code regeneration replaces modified library files).
2024-10-26 Removed since no longer needed.
2024-10-26 Added aileron and elevator conversion values.
2024-10-26 Added unit tests.
2024-10-26 Modified custom HID report output buffer and report descriptor sizes.
2024-10-26 Modified custom HID report descriptor.
2024-10-26 Modified application update and ffb update rates. Added delayMs initialization.
2024-10-26 Added USB packet processing.
2024-10-28 Modified constant force gain.
2024-10-30 Excluded debug directory.
2024-10-30 Removed Debug folder.
2025-08-25 Updated schematic and PCB files for current hardware configuration.
2025-08-25 Added MSFS Force Feedback Controller (Legacy) client for desktop
2025-08-25 Added Force Feedback Yoke Desktop App
    Application is still in development. MSFS Force Feedback Controller Legacy will be migrated to Force Feedback Yoke Desktop App.
2025-08-25 Moved code for other hardware platforms to unused.
2025-08-25 Migrated to STM32H7 platform, added many features.
    - Switched from brushed to brushless motors for both pitch and roll axes. Controller now uses torque control with current sensing
    - Changed encoder hardware to MT6835 for position sensing. Now using AB quadrature output for lower latency.
    - Modified load cell based force feedback assist calculations.
    - Changed USB communication protocol to handle 3 different force types (currently for one axis) using HID interrupt transfers. Switched over to control transfers for configuration.
2025-08-29 Migrated code from MSFSForceFeedbackController (Legacy)
2025-08-29 Adding roll axis support.
2025-08-29 Ignored files.
2025-08-29 Removed duplicate Form1.cs
2025-09-01 Added most features from MSFSForceFeedbackController (Legacy)
2025-09-01 Added support for roll forces over HID.
2025-09-01 Added support for roll forces and roll axis limits.
2025-09-01 Modified velocity PID, added FFB Home Configuration.
2025-09-01 Modified home velocity, changed home center logic.
2025-09-02 Removed max supported forces (unneeded).
2025-09-02 Switched from current to torque units.
2025-09-02 Changed airspeed to indicated airspeed and modified airspeed stiffness damper calculation.
2025-09-02 Roll torque indicators now update.
2025-09-02 Updated comments and removed unneeded commented code.
2025-09-02 Removed unused variables and commented code.
2025-09-02 Added SimpleFOC License.
2025-09-02 Changed remove extension.
2025-09-02 Moved LICENSE_SIMPLEFOC file.
2025-09-02 Create LICENSE
2025-09-02 Updated SimpleFOC license directory.
2025-09-02 Changed naming convention for FFB functions.
2025-09-07 Updated gitignore.
2025-09-07 Removed unneeded struct fields.
2025-09-07 Created SimData class
2025-09-07 Added save button enable logic.
2025-09-07 Added Scale method for decimal type.
2025-09-07 Switched to Range class.
2025-09-07 Cleaned up profile loader and saver code.
2025-09-07 Cleaned up code for updating data and UI.
2025-09-07 Added property changed notifications.
2025-09-07 Added property changed, refined airspeed stiffness calculations.
2025-09-07 Added calibration airspeed parameter.
2025-09-07 Hardware control data now updates with UI.
2025-09-09 Fixed bug with NaN forces on initialization.
2025-09-09 Switched PID tuner DAQ to roll motor.
2025-09-09 Modified roll torque limit, removed current limit defines.
2025-09-09 Fixed bug on device disconnect and connect.
2025-09-09 Modified damper gain divisor.
2025-09-09 Adding tool tips.
2025-09-10 Cleaned up settings table code.
2025-09-10 Divisor is now calculated automatically.
2025-09-12 SettingsTable control now uses ForeColor property.
2025-09-14 Fixed settings table label cut off.
2025-09-14 Refactored code, changed button disabled back color.
2025-09-14 Set auto size to column 2 in settings table.
2026-02-22 Added image of force feedback yoke hardware.
2026-02-22 Added README with project details and features
2026-04-09 Added DTCMRAM section
2026-04-09 Moved time critical variables to DTCM RAM, updated GPIO function naming.
2026-04-09 Updated GPIO function naming.
2026-04-09 Created Load Cell ADC Module and Power Module KiCAD projects.
2026-04-09 Updated .gitignore
2026-04-09 Created new GUI controls.
2026-04-09 Updated Form1.cs
2026-04-09 Created TestDialog.
2026-04-09 Added LPF on motor torque output.
2026-04-09 Misc updates.
